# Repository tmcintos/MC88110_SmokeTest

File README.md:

# MC88110_SmokeTest
 MC88110 CPU Test Board

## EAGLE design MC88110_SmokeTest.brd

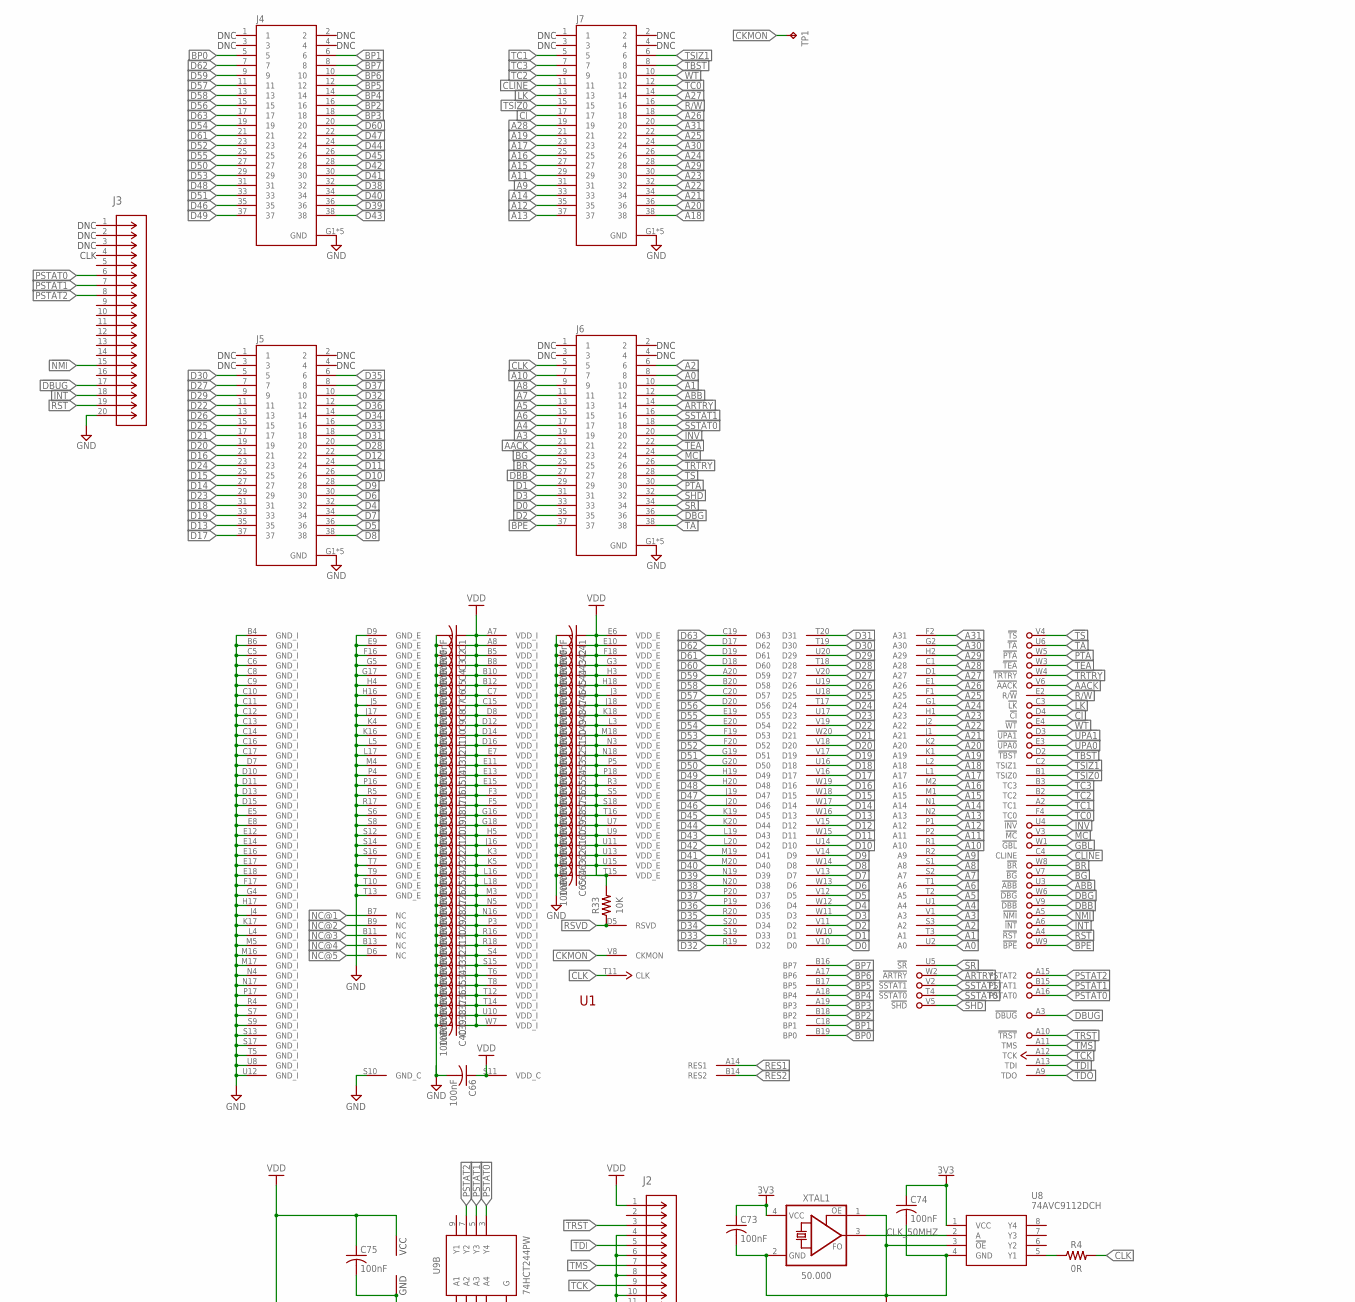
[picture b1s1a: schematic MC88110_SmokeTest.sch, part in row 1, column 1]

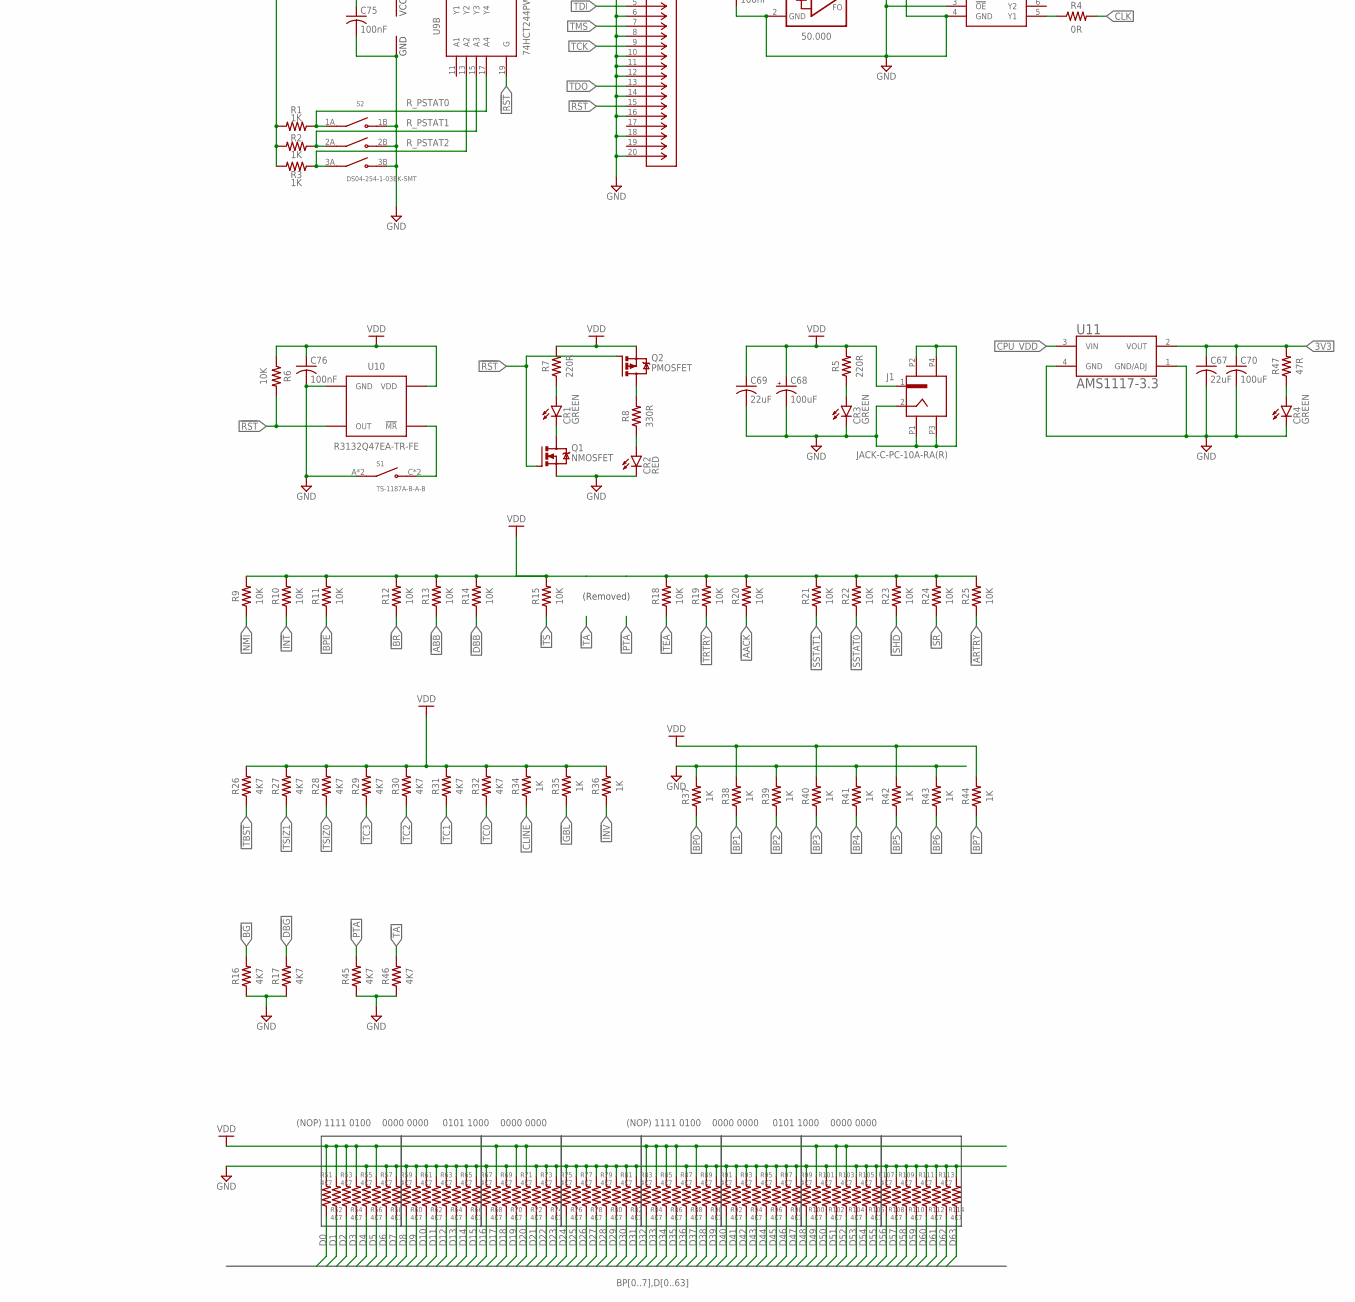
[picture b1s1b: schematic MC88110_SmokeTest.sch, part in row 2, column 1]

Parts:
C1, C2, C3, C4, C5, C6, C7, C8, C9, C10, C11, C12, C13, C14, C15, C16, C17, C18, C19, C20, C21, C22, C23, C24, C25, C26, C27, C28, C29, C30, C31, C32, C33, C34, C35, C36, C37, C38, C39, C40, C41, C42, C43, C44, C45, C46, C47, C48, C49, C50, C51, C52, C53, C54, C55, C56, C57, C58, C59, C60, C61, C62, C63, C64, C65, C66, C73, C74, C75, C76: 100nF; CAPC1608X85; LCSC_PART C14663
C67, C69: 22uF; CAPC1608X85; LCSC_PART C86295
C68: 100uF; CAPMP7343X310N; LCSC_PART C129696
C70: 100uF; CAPC1608X85; LCSC_PART C1955164
CR1, CR3, CR4: GREEN; SML0603; LCSC_PART C12624
CR2: RED; SML0603; LCSC_PART C2286
J1: JACK-C-PC-10A-RA(R); GLOBTECK_JACK-C-PC-10A-RA(R)
J2, J3: 30320-6002HBCONN_30320-6002HB_3MM; CONN_30320-6002HB_3MM; LCSC_PART C5157633
J4, J5, J6, J7: 2-767004-2; TE_2-767004-2; LCSC_PART C2931194
Q1: NMOSFET; SOT23; LCSC_PART C20917
Q2: PMOSFET; SOT23; LCSC_PART C15127
R1, R2, R3, R34, R35, R36, R37, R38, R39, R40, R41, R42, R43, R44: 1K; RESC1608X60; LCSC_PART C21190
R4: 0R; RESC1608X60; LCSC_PART C21189
R5, R7: 220R; RESC1608X60; LCSC_PART C22962
R6, R9, R10, R11, R12, R13, R14, R15, R18, R19, R20, R21, R22, R23, R24, R25, R33: 10K; RESC1608X60; LCSC_PART C25804
R8: 330R; RESC1608X60; LCSC_PART C23138
R16, R17, R26, R27, R28, R29, R30, R31, R32, R45, R46, R51, R52, R53, R54, R55, R56, R57, R58, R59, R60, R61, R62, R63, R64, R65, R66, R67, R68, R69, R70, R71, R72, R73, R74, R75, R76, R77, R78, R79, R80, R81, R82, R83, R84, R85, R86, R87, R88, R89, R90, R91, R92, R93, R94, R95, R96, R97, R98, R99, R100, R101, R102, R103, R104, R105, R106, R107, R108, R109, R110, R111, R112, R113, R114: 4K7; RESC1608X60; LCSC_PART C23162
R47: 47R; RESC1608X60; LCSC_PART C23182
S1: TS-1187A-B-A-B; SW_TS-1187A-B-A-B; LCSC_PART C318884
S2: DS04-254-1-03BK-SMT; SW_DS04-254-1-03BK-SMT; LCSC_PART C129079
TP1: TPTP10R; TP10R
U1: MC88110RC50H; PGA299; LCSC_PART C7187107
U8: 74AVC9112DCH; SOP50P310X100-8N; LCSC_PART C546283
U9: 74HCT244PW; PW20; LCSC_PART C131088
U10: R3132Q47EA-TR-FE; R3132Q; LCSC_PART C2461150
U11: AMS1117-3.3; SOT229P700X180-4N; LCSC_PART C6186
XTAL1: 50.000; OSCCC320X250X90; LCSC_PART C5203552

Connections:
3V3: C67.1, C70.1, C73.1, C74.1, R47.2, U8.1 (VCC), U11.2 (VOUT), XTAL1.4 (VCC)
!AACK: J6.21, R20.1, U1.V6 (!AACK)
!ABB: J6.12, R13.1, U1.U3 (!ABB)
!ARTRY: J6.14, R25.1, U1.W2 (!ARTRY)
!BG: J6.23, R16.2, U1.V7 (!BG)
!BPE: J6.37, R11.1, U1.W9 (!BPE)
!BR: J6.25, R12.1, U1.W8 (!BR)
!CI: J7.17, U1.D4 (!CI)
!DBB: J6.27, R14.1, U1.V9 (!DBB)
!DBG: J6.36, R17.2, U1.W6 (!DBG)
!DBUG: J3.17, U1.A3 (!DBUG)
!GBL: R35.1, U1.W1 (!GBL)
!INT: J3.18, R10.1, U1.A6 (!INT)
!INV: J6.20, R36.1, U1.U4 (!INV)
!LK: J7.13, U1.C3 (!LK)
!MC: J6.24, U1.V3 (!MC)
!MR: S1.C (NO), S1.D (NO), U10.P$3 (!MR)
!NMI: J3.15, R9.1, U1.A5 (!NMI)
!PTA: J6.30, R45.2, U1.W5 (!PTA)
!RST: J2.15, J3.19, Q1.1 (G), Q2.1 (G), R6.2, U1.A4 (!RST), U9.19 (G), U10.P$2 (OUT)
!SHD: J6.32, R23.1, U1.V5 (!SHD)
!SR: J6.34, R24.1, U1.U5 (!SR)
!SSTAT0: J6.18, R22.1, U1.T4 (!SSTAT0)
!SSTAT1: J6.16, R21.1, U1.V2 (!SSTAT1)
!TA: J6.38, R46.2, U1.U6 (!TA)
!TBST: J7.8, R26.1, U1.D2 (!TBST)
!TEA: J6.22, R18.1, U1.W3 (!TEA)
!TRST: J2.3, U1.A10 (!TRST)
!TRTRY: J6.26, R19.1, U1.W4 (!TRTRY)
!TS: J6.28, R15.1, U1.V4 (!TS)
!UPA0: U1.E3 (!UPA0)
!UPA1: U1.D3 (!UPA1)
!WT: J7.10, U1.E4 (!WT)
A0: J6.8, U1.U2 (A0)
A1: J6.10, U1.T3 (A1)
A2: J6.6, U1.S3 (A2)
A3: J6.19, U1.V1 (A3)
A4: J6.17, U1.U1 (A4)
A5: J6.13, U1.T2 (A5)
A6: J6.15, U1.T1 (A6)
A7: J6.11, U1.S2 (A7)
A8: J6.9, U1.S1 (A8)
A9: J7.31, U1.R2 (A9)
A10: J6.7, U1.R1 (A10)
A11: J7.29, U1.P2 (A11)
A12: J7.35, U1.P1 (A12)
A13: J7.37, U1.N2 (A13)
A14: J7.33, U1.N1 (A14)
A15: J7.27, U1.M1 (A15)
A16: J7.25, U1.M2 (A16)
A17: J7.23, U1.L1 (A17)
A18: J7.38, U1.L2 (A18)
A19: J7.21, U1.K1 (A19)
A20: J7.36, U1.K2 (A20)
A21: J7.34, U1.J1 (A21)
A22: J7.32, U1.J2 (A22)
A23: J7.30, U1.H1 (A23)
A24: J7.26, U1.G1 (A24)
A25: J7.22, U1.F1 (A25)
A26: J7.18, U1.E1 (A26)
A27: J7.14, U1.D1 (A27)
A28: J7.19, U1.C1 (A28)
A29: J7.28, U1.H2 (A29)
A30: J7.24, U1.G2 (A30)
A31: J7.20, U1.F2 (A31)
BP0: J4.5, R37.1, U1.B19 (BP0)
BP1: J4.6, R38.1, U1.C18 (BP1)
BP2: J4.16, R39.1, U1.B18 (BP2)
BP3: J4.18, R40.1, U1.A19 (BP3)
BP4: J4.14, R41.1, U1.A18 (BP4)
BP5: J4.12, R42.1, U1.B17 (BP5)
BP6: J4.10, R43.1, U1.A17 (BP6)
BP7: J4.8, R44.1, U1.B16 (BP7)
CKMON: TP1.TP, U1.V8 (CKMON)
CLINE: J7.11, R34.1, U1.C4 (CLINE)
CLK: J6.5, R4.2, U1.T11 (CLK)
CLK_50MHZ: U8.2 (A), XTAL1.3 (FO)
CPU_VDD: C1.1, C2.1, C3.1, C4.1, C5.1, C6.1, C7.1, C8.1, C9.1, C10.1, C11.1, C12.1, C13.1, C14.1, C15.1, C16.1, C17.1, C18.1, C19.1, C20.1, C21.1, C22.1, C23.1, C24.1, C25.1, C26.1, C27.1, C28.1, C29.1, C30.1, C31.1, C32.1, C33.1, C34.1, C35.1, C36.1, C37.1, C38.1, C39.1, C40.1, C41.1, C42.1, C43.1, C44.1, C45.1, C46.1, C47.1, C48.1, C49.1, C50.1, C51.1, C52.1, C53.1, C54.1, C55.1, C56.1, C57.1, C58.1, C59.1, C60.1, C61.1, C62.1, C63.1, C64.1, C65.1, C66.1, C68.1 (+), C69.1, C75.1, C76.1, J1.1, J2.1, Q2.2 (S), R1.2, R2.2, R3.2, R5.2, R6.1, R7.2, R9.2, R10.2, R11.2, R12.2, R13.2, R14.2, R15.2, R18.2, R19.2, R20.2, R21.2, R22.2, R23.2, R24.2, R25.2, R26.2, R27.2, R28.2, R29.2, R30.2, R31.2, R32.2, R33.2, R34.2, R35.2, R36.2, R38.2, R40.2, R42.2, R44.2, R51.2, R52.2, R53.2, R54.2, R56.2, R68.2, R70.2, R71.2, R83.2, R84.2, R85.2, R86.2, R88.2, R100.2, R102.2, R103.2, U1.A7 (VDD_I), U1.A8 (VDD_I), U1.B5 (VDD_I), U1.B8 (VDD_I), U1.B10 (VDD_I), U1.B12 (VDD_I), U1.C7 (VDD_I), U1.C15 (VDD_I), U1.D8 (VDD_I), U1.D12 (VDD_I), U1.D14 (VDD_I), U1.D16 (VDD_I), U1.E6 (VDD_E), U1.E7 (VDD_I), U1.E10 (VDD_E), U1.E11 (VDD_I), U1.E13 (VDD_I), U1.E15 (VDD_I), U1.F3 (VDD_I), U1.F5 (VDD_I), U1.F18 (VDD_E), U1.G3 (VDD_E), U1.G16 (VDD_I), U1.G18 (VDD_I), U1.H3 (VDD_E), U1.H5 (VDD_I), U1.H18 (VDD_E), U1.J3 (VDD_E), U1.J16 (VDD_I), U1.J18 (VDD_E), U1.K3 (VDD_I), U1.K5 (VDD_I), U1.K18 (VDD_E), U1.L3 (VDD_E), U1.L16 (VDD_I), U1.L18 (VDD_I), U1.M3 (VDD_I), U1.M18 (VDD_E), U1.N3 (VDD_E), U1.N5 (VDD_I), U1.N16 (VDD_I), U1.N18 (VDD_E), U1.P3 (VDD_I), U1.P5 (VDD_E), U1.P18 (VDD_E), U1.R3 (VDD_E), U1.R16 (VDD_I), U1.R18 (VDD_I), U1.S4 (VDD_I), U1.S5 (VDD_E), U1.S11 (VDD_C), U1.S15 (VDD_I), U1.S18 (VDD_E), U1.T6 (VDD_I), U1.T8 (VDD_I), U1.T12 (VDD_I), U1.T14 (VDD_I), U1.T15 (VDD_E), U1.T16 (VDD_E), U1.U7 (VDD_E), U1.U9 (VDD_E), U1.U10 (VDD_I), U1.U11 (VDD_E), U1.U13 (VDD_E), U1.U15 (VDD_E), U1.W7 (VDD_I), U9.20 (VCC), U10.P$4 (VDD), U11.3 (VIN)
D0: J6.33, R51.1, U1.V10 (D0)
D1: J6.29, R52.1, U1.W10 (D1)
D2: J6.35, R53.1, U1.V11 (D2)
D3: J6.31, R54.1, U1.W11 (D3)
D4: J5.32, R55.1, U1.W12 (D4)
D5: J5.36, R56.1, U1.V12 (D5)
D6: J5.30, R57.1, U1.W13 (D6)
D7: J5.34, R58.1, U1.V13 (D7)
D8: J5.38, R59.1, U1.W14 (D8)
D9: J5.28, R60.1, U1.V14 (D9)
D10: J5.26, R61.1, U1.U14 (D10)
D11: J5.24, R62.1, U1.W15 (D11)
D12: J5.22, R63.1, U1.V15 (D12)
D13: J5.35, R64.1, U1.W16 (D13)
D14: J5.27, R65.1, U1.W17 (D14)
D15: J5.25, R66.1, U1.W18 (D15)
D16: J5.21, R67.1, U1.W19 (D16)
D17: J5.37, R68.1, U1.V16 (D17)
D18: J5.31, R69.1, U1.U16 (D18)
D19: J5.33, R70.1, U1.V17 (D19)
D20: J5.19, R71.1, U1.V18 (D20)
D21: J5.17, R72.1, U1.W20 (D21)
D22: J5.11, R73.1, U1.V19 (D22)
D23: J5.29, R74.1, U1.U17 (D23)
D24: J5.23, R75.1, U1.T17 (D24)
D25: J5.15, R76.1, U1.U18 (D25)
D26: J5.13, R77.1, U1.U19 (D26)
D27: J5.7, R78.1, U1.V20 (D27)
D28: J5.20, R79.1, U1.T18 (D28)
D29: J5.9, R80.1, U1.U20 (D29)
D30: J5.5, R81.1, U1.T19 (D30)
D31: J5.18, R82.1, U1.T20 (D31)
D32: J5.10, R83.1, U1.R19 (D32)
D33: J5.16, R84.1, U1.S19 (D33)
D34: J5.14, R85.1, U1.S20 (D34)
D35: J5.6, R86.1, U1.R20 (D35)
D36: J5.12, R87.1, U1.P19 (D36)
D37: J5.8, R88.1, U1.P20 (D37)
D38: J4.32, R89.1, U1.N20 (D38)
D39: J4.36, R90.1, U1.N19 (D39)
D40: J4.34, R91.1, U1.M20 (D40)
D41: J4.30, R92.1, U1.M19 (D41)
D42: J4.28, R93.1, U1.L20 (D42)
D43: J4.38, R94.1, U1.L19 (D43)
D44: J4.24, R95.1, U1.K20 (D44)
D45: J4.26, R96.1, U1.K19 (D45)
D46: J4.35, R97.1, U1.J20 (D46)
D47: J4.22, R98.1, U1.J19 (D47)
D48: J4.31, R99.1, U1.H20 (D48)
D49: J4.37, R100.1, U1.H19 (D49)
D50: J4.27, R101.1, U1.G20 (D50)
D51: J4.33, R102.1, U1.G19 (D51)
D52: J4.23, R103.1, U1.F20 (D52)
D53: J4.29, R104.1, U1.F19 (D53)
D54: J4.19, R105.1, U1.E20 (D54)
D55: J4.25, R106.1, U1.E19 (D55)
D56: J4.15, R107.1, U1.D20 (D56)
D57: J4.11, R108.1, U1.C20 (D57)
D58: J4.13, R109.1, U1.B20 (D58)
D59: J4.9, R110.1, U1.A20 (D59)
D60: J4.20, R111.1, U1.D18 (D60)
D61: J4.21, R112.1, U1.D19 (D61)
D62: J4.7, R113.1, U1.D17 (D62)
D63: J4.17, R114.1, U1.C19 (D63)
GND: C1.2, C2.2, C3.2, C4.2, C5.2, C6.2, C7.2, C8.2, C9.2, C10.2, C11.2, C12.2, C13.2, C14.2, C15.2, C16.2, C17.2, C18.2, C19.2, C20.2, C21.2, C22.2, C23.2, C24.2, C25.2, C26.2, C27.2, C28.2, C29.2, C30.2, C31.2, C32.2, C33.2, C34.2, C35.2, C36.2, C37.2, C38.2, C39.2, C40.2, C41.2, C42.2, C43.2, C44.2, C45.2, C46.2, C47.2, C48.2, C49.2, C50.2, C51.2, C52.2, C53.2, C54.2, C55.2, C56.2, C57.2, C58.2, C59.2, C60.2, C61.2, C62.2, C63.2, C64.2, C65.2, C66.2, C67.2, C68.2 (-), C69.2, C70.2, C73.2, C74.2, C75.2, C76.2, CR2.C, CR3.C, CR4.C, J1.2, J1.P1, J1.P2, J1.P3, J1.P4, J2.4, J2.6, J2.8, J2.10, J2.11, J2.12, J2.14, J2.16, J2.18, J2.20, J3.20, J4.G1 (GND), J4.G2 (GND), J4.G3 (GND), J4.G4 (GND), J4.G5 (GND), J5.G1 (GND), J5.G2 (GND), J5.G3 (GND), J5.G4 (GND), J5.G5 (GND), J6.G1 (GND), J6.G2 (GND), J6.G3 (GND), J6.G4 (GND), J6.G5 (GND), J7.G1 (GND), J7.G2 (GND), J7.G3 (GND), J7.G4 (GND), J7.G5 (GND), Q1.2 (S), R16.1, R17.1, R37.2, R39.2, R41.2, R43.2, R45.1, R46.1, R55.2, R57.2, R58.2, R59.2, R60.2, R61.2, R62.2, R63.2, R64.2, R65.2, R66.2, R67.2, R69.2, R72.2, R73.2, R74.2, R75.2, R76.2, R77.2, R78.2, R79.2, R80.2, R81.2, R82.2, R87.2, R89.2, R90.2, R91.2, R92.2, R93.2, R94.2, R95.2, R96.2, R97.2, R98.2, R99.2, R101.2, R104.2, R105.2, R106.2, R107.2, R108.2, R109.2, R110.2, R111.2, R112.2, R113.2, R114.2, S1.A (COM), S1.B (COM), S2.1B (NO1), S2.2B (NO2), S2.3B (NO3), U1.B4 (GND_I), U1.B6 (GND_I), U1.C5 (GND_I), U1.C6 (GND_I), U1.C8 (GND_I), U1.C9 (GND_I), U1.C10 (GND_I), U1.C11 (GND_I), U1.C12 (GND_I), U1.C13 (GND_I), U1.C14 (GND_I), U1.C16 (GND_I), U1.C17 (GND_I), U1.D7 (GND_I), U1.D9 (GND_E), U1.D10 (GND_I), U1.D11 (GND_I), U1.D13 (GND_I), U1.D15 (GND_I), U1.E5 (GND_I), U1.E8 (GND_I), U1.E9 (GND_E), U1.E12 (GND_I), U1.E14 (GND_I), U1.E16 (GND_I), U1.E17 (GND_I), U1.E18 (GND_I), U1.F16 (GND_E), U1.F17 (GND_I), U1.G4 (GND_I), U1.G5 (GND_E), U1.G17 (GND_E), U1.H4 (GND_E), U1.H16 (GND_E), U1.H17 (GND_I), U1.J4 (GND_I), U1.J5 (GND_E), U1.J17 (GND_E), U1.K4 (GND_E), U1.K16 (GND_E), U1.K17 (GND_I), U1.L4 (GND_I), U1.L5 (GND_E), U1.L17 (GND_E), U1.M4 (GND_E), U1.M5 (GND_I), U1.M16 (GND_I), U1.M17 (GND_I), U1.N4 (GND_I), U1.N17 (GND_I), U1.P4 (GND_E), U1.P16 (GND_E), U1.P17 (GND_I), U1.R4 (GND_I), U1.R5 (GND_E), U1.R17 (GND_E), U1.S6 (GND_E), U1.S7 (GND_I), U1.S8 (GND_E), U1.S9 (GND_I), U1.S10 (GND_C), U1.S12 (GND_E), U1.S13 (GND_I), U1.S14 (GND_E), U1.S16 (GND_E), U1.S17 (GND_I), U1.T5 (GND_I), U1.T7 (GND_E), U1.T9 (GND_E), U1.T10 (GND_E), U1.T13 (GND_E), U1.U8 (GND_I), U1.U12 (GND_I), U8.3 (!OE), U8.4 (GND), U9.10 (GND), U10.P$1 (GND), U11.1 (GND/ADJ), U11.4 (GND), XTAL1.1 (OE), XTAL1.2 (GND)
LED1+: CR1.A, R7.1
LED1+1: CR3.A, R5.1
LED1+2: CR4.A, R47.1
LED1-: CR1.C, Q1.3 (D)
LED2+: CR2.A, R8.1
LV_CLK_CPU_R: R4.1, U8.5 (Y1)
NC@1: U1.B7 (NC)
NC@2: U1.B9 (NC)
NC@3: U1.B11 (NC)
NC@4: U1.B13 (NC)
NC@5: U1.D6 (NC)
PSTAT0: J3.6, U1.A16 (PSTAT0), U9.3 (Y4)
PSTAT1: J3.7, U1.B15 (PSTAT1), U9.5 (Y3)
PSTAT2: J3.8, U1.A15 (PSTAT2), U9.7 (Y2)
R11+: Q2.3 (D), R8.2
R/!W: J7.16, U1.E2 (R/!W)
RES1: U1.A14 (RES1)
RES2: U1.B14 (RES2)
RSVD: R33.1, U1.D5 (RSVD)
R_PSTAT0: R1.1, S2.1A (COM1), U9.17 (A4)
R_PSTAT1: R2.1, S2.2A (COM2), U9.15 (A3)
R_PSTAT2: R3.1, S2.3A (COM3), U9.13 (A2)
TC0: J7.12, R32.1, U1.F4 (TC0)
TC1: J7.5, R31.1, U1.A2 (TC1)
TC2: J7.9, R30.1, U1.B2 (TC2)
TC3: J7.7, R29.1, U1.B3 (TC3)
TCK: J2.9, U1.A12 (TCK)
TDI: J2.5, U1.A13 (TDI)
TDO: J2.13, U1.A9 (TDO)
TMS: J2.7, U1.A11 (TMS)
TSIZ0: J7.15, R28.1, U1.B1 (TSIZ0)
TSIZ1: J7.6, R27.1, U1.C2 (TSIZ1)

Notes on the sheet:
DNC
CLK
(Removed)
(NOP) 1111 0100 0000 0000 0101 1000 0000 0000

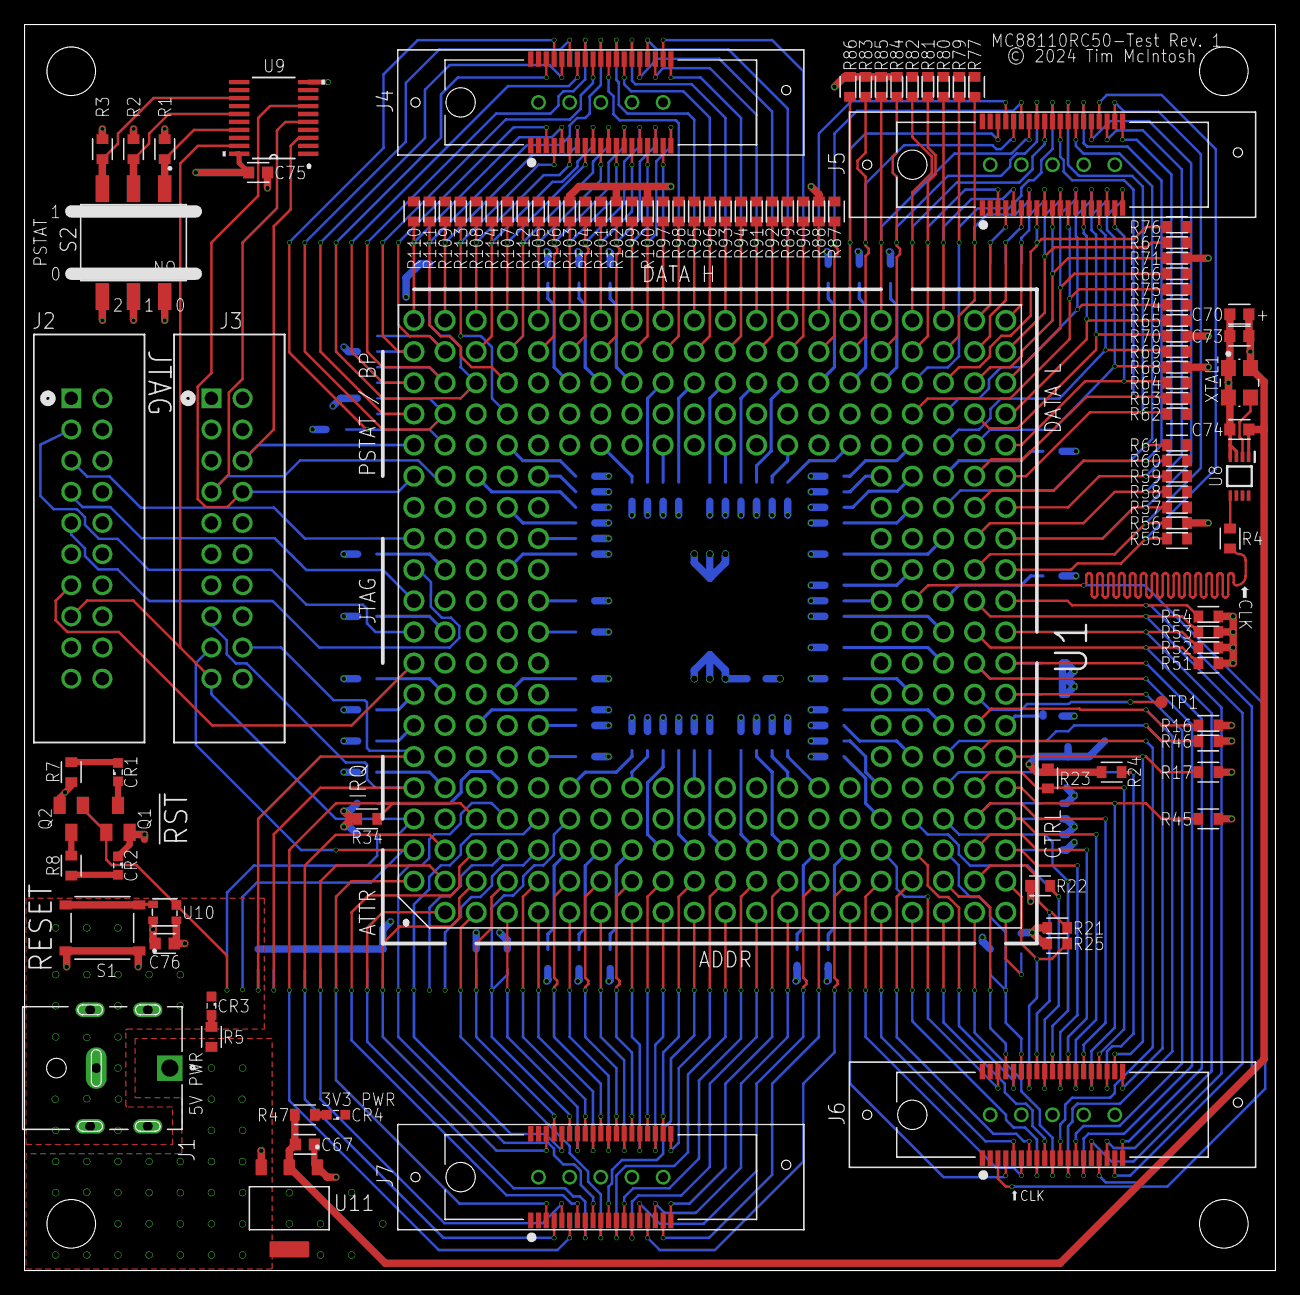
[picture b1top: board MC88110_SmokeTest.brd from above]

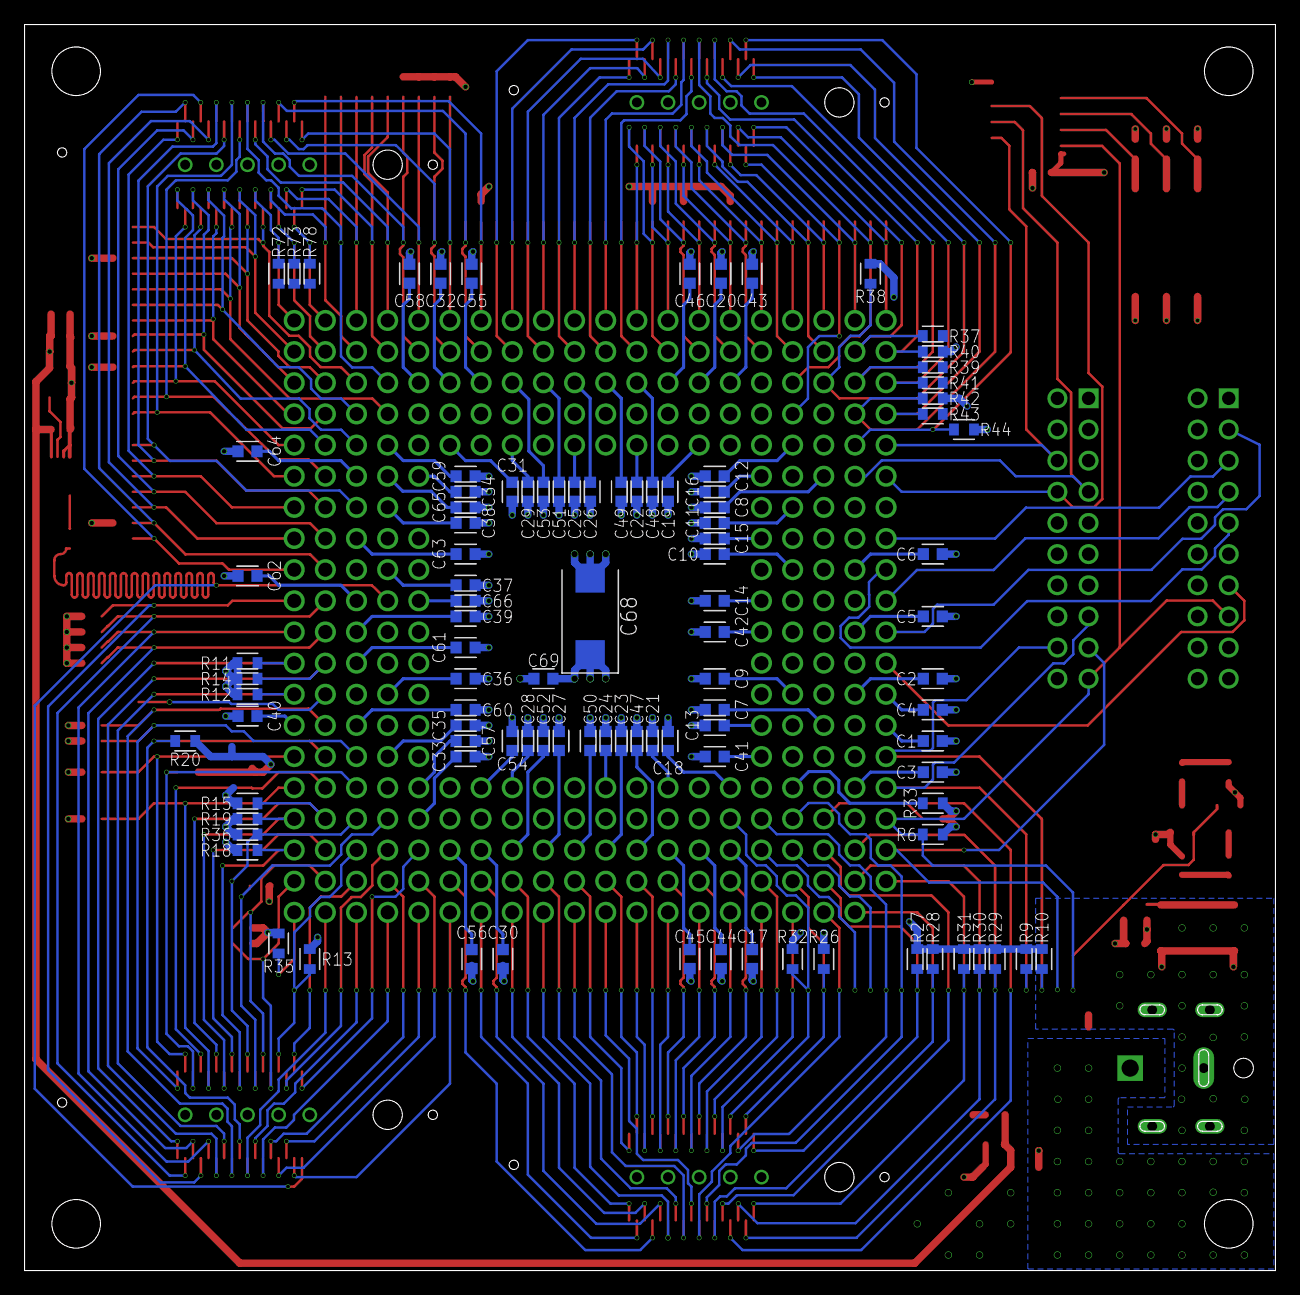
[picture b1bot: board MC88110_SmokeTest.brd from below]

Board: 4 copper layers, 102.0 x 101.6 mm, 207 parts (100 on the bottom side), 166 nets.

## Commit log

2025-04-10 v91 EAGLE9.X export
2025-04-10 Create Rework_Errata.pdf
    Add rework/errata document for the version that I had manufactured by JLCPCB last year (v81), which had a few issues.
    I don’t think I corrected all of the issues in the schematic/PCB before pausing work last year. From the Fusion history, it appears that I may only have corrected the problem with CR- described in st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

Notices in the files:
MC88110_SmokeTest.brd:
© 2024 Tim McIntosh
parts and their libraries:
COPYRIGHT: Copyright (C) 2024 Ultra Librarian. All rights reserved.
